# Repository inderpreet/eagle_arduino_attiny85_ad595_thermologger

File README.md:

# Thermologger

What happens when you put an ATTINY85 and an AD595 thermocouple amplifier together? This! It is a relatively simplistic project with the PCB made in Eagle. The code is a work in progress so yeah.

## Dependencies

* Autodesk Eagle

## Author and License

Designed by [Inderpreet Singh](https://inderpreet.github.io)

This software may be distributed and modified under the terms of the GNU
General Public License version 2 (GPL2) as published by the Free Software
Foundation and appearing in the file LICENSE.TXT included in the packaging of
this file. Please note that GPL2 Section 2[b] requires that all works based
on this software must also be made publicly available under the terms of
the GPL2 ("Copyleft").

We put a lot of time and effort into our project and hence this copyright 
notice ensures that people contribute as well as each contribution is 
acknowledged. Please retain this original notice and if you make changes
please document them below along with your details.

The latest copy of this project/library can be found at: 
https://github.com/inderpreet/

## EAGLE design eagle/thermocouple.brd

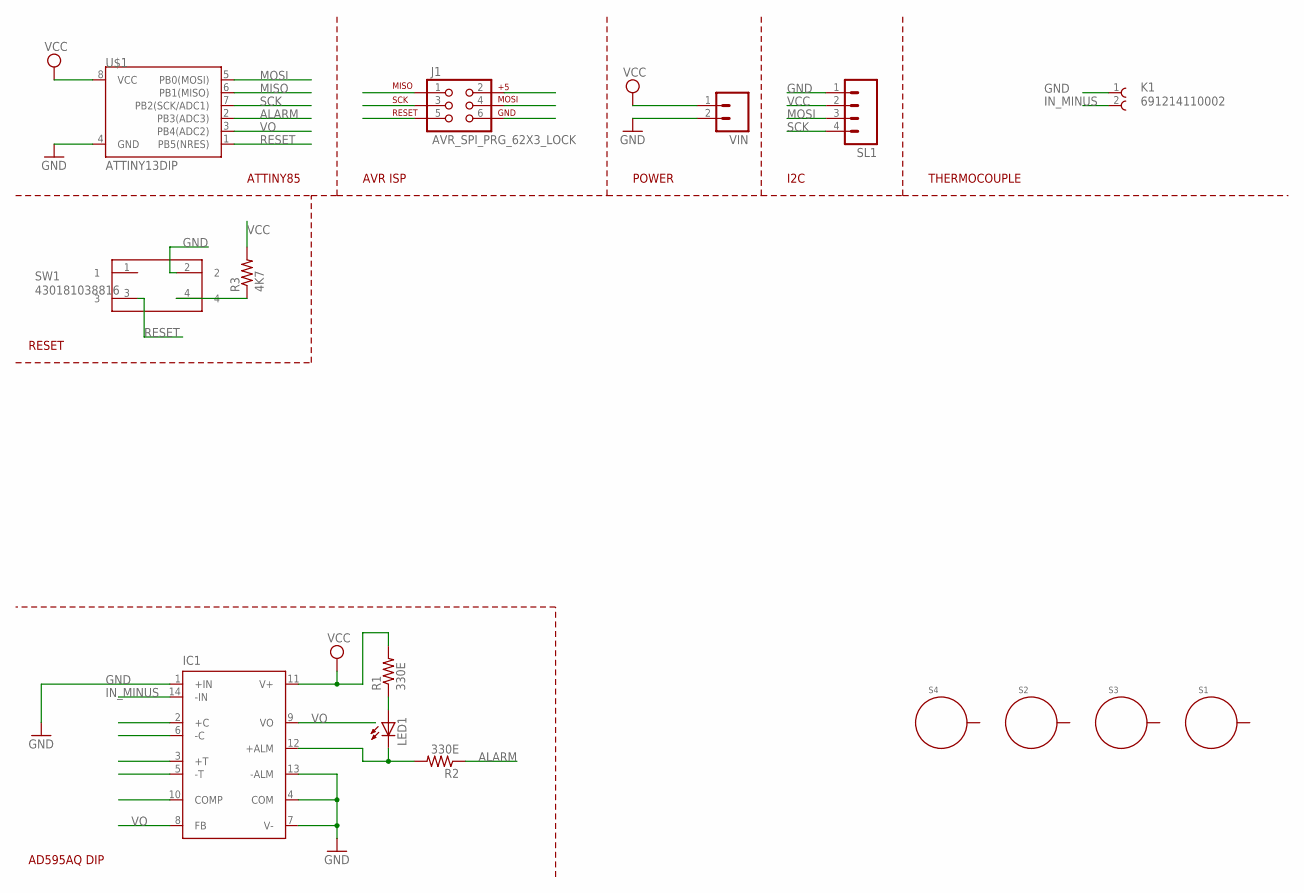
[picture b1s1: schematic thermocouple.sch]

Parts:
IC1: AD595; DIL14
J1: AVR_SPI_PRG_62X3_LOCK; 2X3_LOCK
K1: 691214110002
LED1: LEDCHIPLED_0805; CHIPLED_0805
R1, R2: 330E; M0805
R3: 4K7; M0805
S1, S2, S3, S4: STANDOFF_ELECTRICAL; STANDOFF-ELECTRICAL
SL1: M04; 04P
SW1: 430181038816
U$1: ATTINY13DIP; DIP08
VIN: M02; 02P

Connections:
ALARM: R2.1, U$1.2 (PB3(ADC3))
GND: IC1.1 (+IN), IC1.4 (COM), IC1.7 (V-), IC1.13 (-ALM), J1.6, K1.1, SL1.1, SW1.2, U$1.4 (GND), VIN.2
IN_MINUS: IC1.14 (-IN), K1.2
MISO: J1.1, U$1.6 (PB1(MISO))
MOSI: J1.4, SL1.3, U$1.5 (PB0(MOSI))
unnamed: LED1.A, R1.1
unnamed: IC1.12 (+ALM), LED1.C, R2.2
unnamed: R3.1, SW1.4
RESET: J1.5, SW1.3, U$1.1 (PB5(NRES))
SCK: J1.3, SL1.4, U$1.7 (PB2(SCK/ADC1))
VCC: IC1.11 (V+), J1.2, R1.2, R3.2, SL1.2, U$1.8 (VCC), VIN.1
VO: IC1.8 (FB), IC1.9 (VO), U$1.3 (PB4(ADC2))

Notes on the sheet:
AD595AQ DIP
RESET
ATTINY85
AVR ISP
POWER
I2C
THERMOCOUPLE

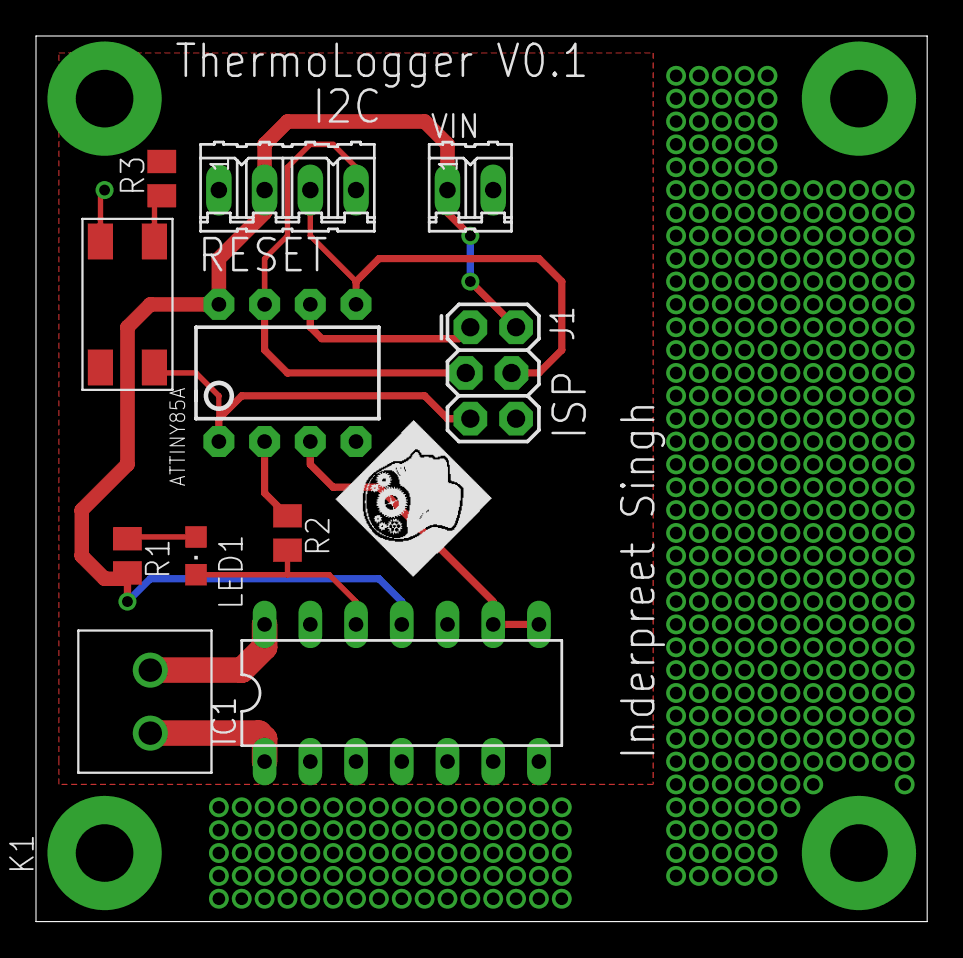
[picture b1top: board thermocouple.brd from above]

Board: 2 copper layers, 49.5 x 49.2 mm, 16 parts (0 on the bottom side), 12 nets.

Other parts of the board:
U$2: LOGO2

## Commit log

2018-05-16 Inital Commit:
2018-05-16 Fabed using OSHPARK

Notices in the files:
parts and their libraries:
SparkFun-Connectors: Licensing: CC v3.0 Share-Alike You are welcome to use this library for commercial purposes.
Wuerth_Elektronik_eiCan_Terminal_Blocks_: Copyright: Würth Elektronik
